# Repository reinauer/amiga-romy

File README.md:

# Amiga Romy

ROMY is a small add-on PCB that enables Amiga 3000 / 4000 computers to use 1MB (or larger) Kickstart chips.

This project aims at iterating and improving the existing Romy designs.

# Software

Look in the [`software`](software/) directory for a bunch of scripts to create a nice 1MB ROM
image for you.

There's also a small program to create parametrized PLCC plug footprints for
KiCAD.

# Logic

The [`logic`](logic/) directory contains the contents for the GAL 22V10. If you want to
build a ROMY yourself, you will need to program this before soldering your GAL
down.

# Hardware

In the [`hardware`](hardware/) directory you will find the kicad schematics and PCB for the
latest versions of ROMY:

## Amiga 4000 Romy

This version was the first one I made. It fits snugly on top of a soldered-down
Fat Gary. The GAL is a PLCC-28 ATF22V10C type. This design is the most similar
to the original Romy.

## Amiga 3000 Romy

This version is a revamp of the A3000 Romy. On the A3000 Fat Gary is socketed
using a through-hole PLCC-84 socket. Previous designs have required to unsolder
the socket, and solder a PCB between a socket and the mainboard, in some
variants adding a capacitor on the bottom of the mainboard.

This new design uses a PLCC-28 ATF22V10C GAL instead of the DIP version on
older Amiga 3000 designs. This is convenient because it lets you exchange GALs
between the A3000 and A4000 version.

To prevent having to solder on the A3000 board, I am using PLCC plugs (such as
the APW9328 from adapt-plus.com).

## Ultimate Romy

Now this gets exciting. PLCC parts are annoying to solder and fairly big. So I
skipped DIP and SOIC and went straight to the TSOP version of the ATF22V10C.
The small footprint of this part allows to create a single board for Amiga 3000
and Amiga 4000 machines.

* If you want to build an A4000 Romy with this design, put a PLCC84 socket on the
back of the PCB, and a capacitor and GAL on the front.
* To build the A3000 version, instead solder a PLCC-84 socket on the front of
the PCB, and solder the cap and GAL on the bottom. Then solder the PLCC plug
over the components.

This design is barely wider than Fat Gary itself and adds the same
functionality as the other ROMYs with minimal impact.

# ROM Extender

The ROM Extender allows the use of 4MB ROM space in an A3000/4000 with the
Ultimate ROMY r6 or newer versions of the A3000 ROMY. You need to connect the
additional address pins between the extender and your ROMY.

When assembling, make sure to optimize for height of the adapter as your
accelerator might have trouble fitting on the A4000.

# Credits

Romy has been developed in the past by speedgeek and Cosmos. Anton Gale kept
the designs alive on OSHPark. Thanks to John Floren for an amazing Amiga 3000,
and to Acill for patiently teaching soldering skills to firmware engineers like
me and for building an awesome community.

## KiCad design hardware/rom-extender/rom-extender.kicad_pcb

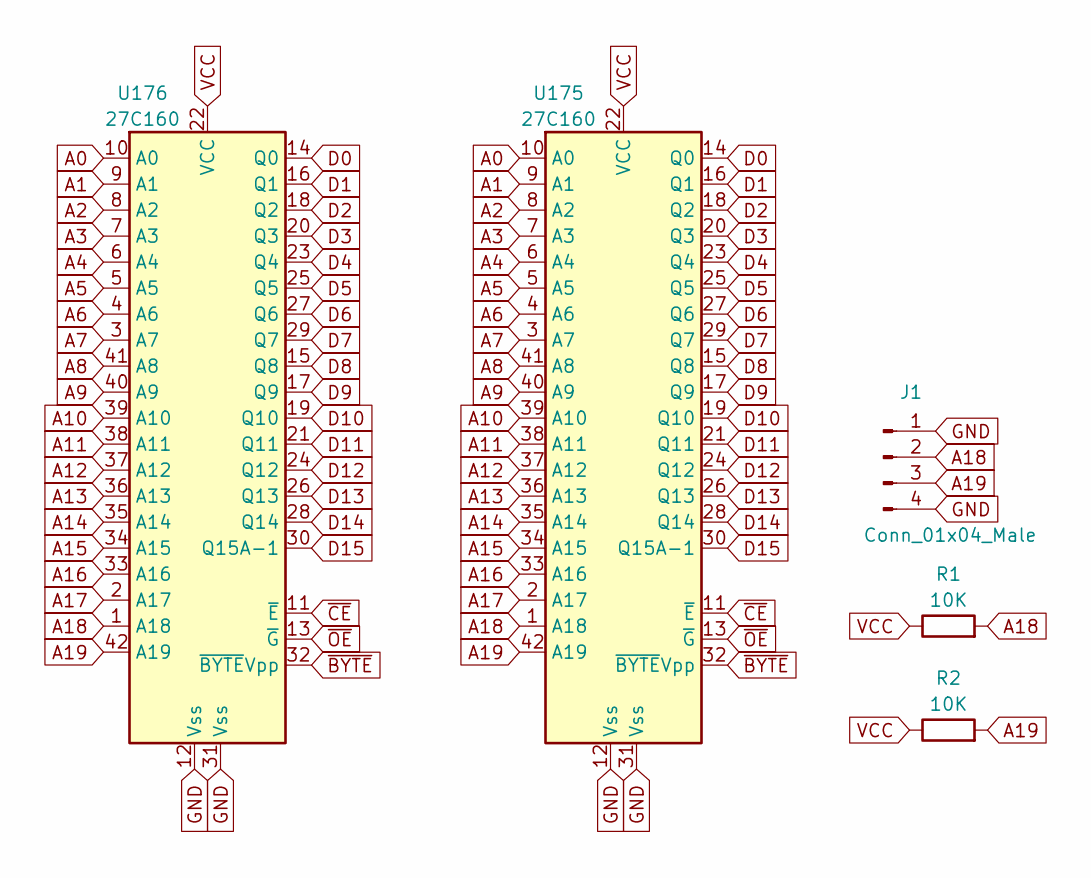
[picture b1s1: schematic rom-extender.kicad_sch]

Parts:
J1: Conn_01x04_Male; PinHeader_1x04_P2.54mm_Vertical
R1, R2: 10K; R_0805_2012Metric_Pad1.20x1.40mm_HandSolder
U175, U176: 27C160; DIP-42_W15.24mm

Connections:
A0: U175.10 (A0), U176.10 (A0)
A1: U175.9 (A1), U176.9 (A1)
A2: U175.8 (A2), U176.8 (A2)
A3: U175.7 (A3), U176.7 (A3)
A4: U175.6 (A4), U176.6 (A4)
A5: U175.5 (A5), U176.5 (A5)
A6: U175.4 (A6), U176.4 (A6)
A7: U175.3 (A7), U176.3 (A7)
A8: U175.41 (A8), U176.41 (A8)
A9: U175.40 (A9), U176.40 (A9)
A10: U175.39 (A10), U176.39 (A10)
A11: U175.38 (A11), U176.38 (A11)
A12: U175.37 (A12), U176.37 (A12)
A13: U175.36 (A13), U176.36 (A13)
A14: U175.35 (A14), U176.35 (A14)
A15: U175.34 (A15), U176.34 (A15)
A16: U175.33 (A16), U176.33 (A16)
A17: U175.2 (A17), U176.2 (A17)
A18: J1.2, R1.2, U175.1 (A18), U176.1 (A18)
A19: J1.3, R2.2, U175.42 (A19), U176.42 (A19)
D0: U175.14 (Q0), U176.14 (Q0)
D1: U175.16 (Q1), U176.16 (Q1)
D2: U175.18 (Q2), U176.18 (Q2)
D3: U175.20 (Q3), U176.20 (Q3)
D4: U175.23 (Q4), U176.23 (Q4)
D5: U175.25 (Q5), U176.25 (Q5)
D6: U175.27 (Q6), U176.27 (Q6)
D7: U175.29 (Q7), U176.29 (Q7)
D8: U175.15 (Q8), U176.15 (Q8)
D9: U175.17 (Q9), U176.17 (Q9)
D10: U175.19 (Q10), U176.19 (Q10)
D11: U175.21 (Q11), U176.21 (Q11)
D12: U175.24 (Q12), U176.24 (Q12)
D13: U175.26 (Q13), U176.26 (Q13)
D14: U175.28 (Q14), U176.28 (Q14)
D15: U175.30 (Q15A-1), U176.30 (Q15A-1)
GND: J1.1, J1.4, U175.12 (Vss), U175.31 (Vss), U176.12 (Vss), U176.31 (Vss)
VCC: R1.1, R2.1, U175.22 (VCC), U176.22 (VCC)
~BYTE: U175.32 (~BYTE~Vpp), U176.32 (~BYTE~Vpp)
~CE: U175.11 (~E), U176.11 (~E)
~OE: U175.13 (~G), U176.13 (~G)

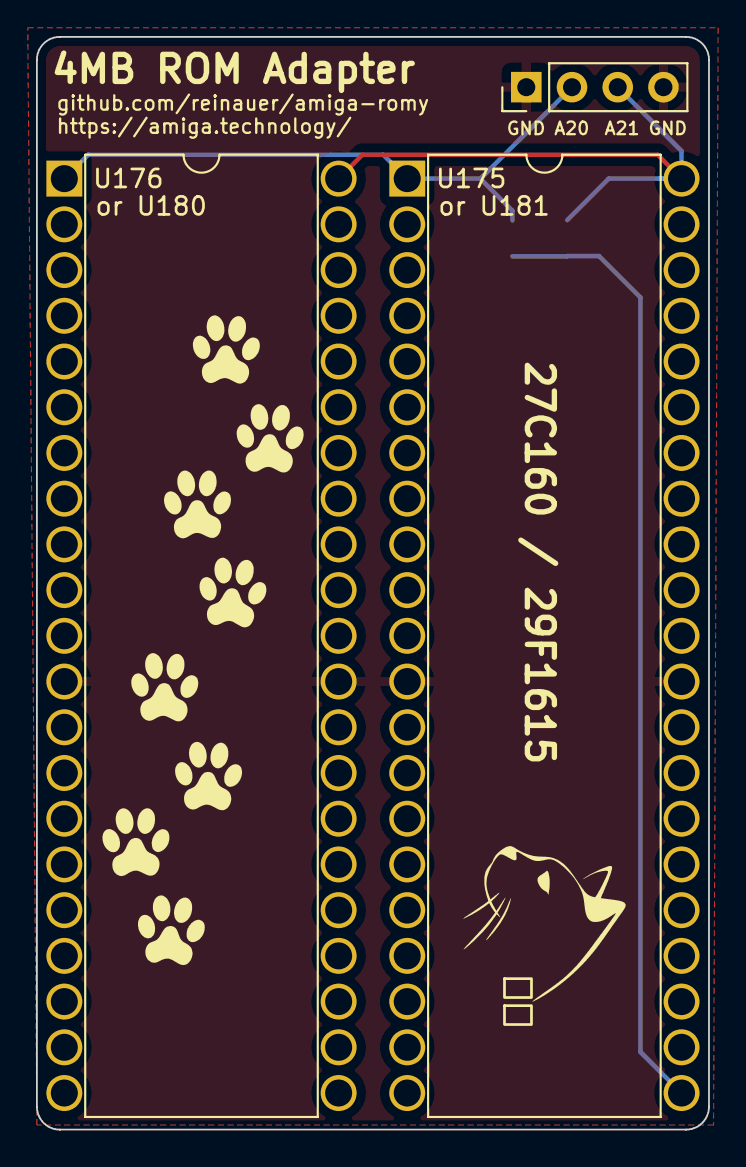
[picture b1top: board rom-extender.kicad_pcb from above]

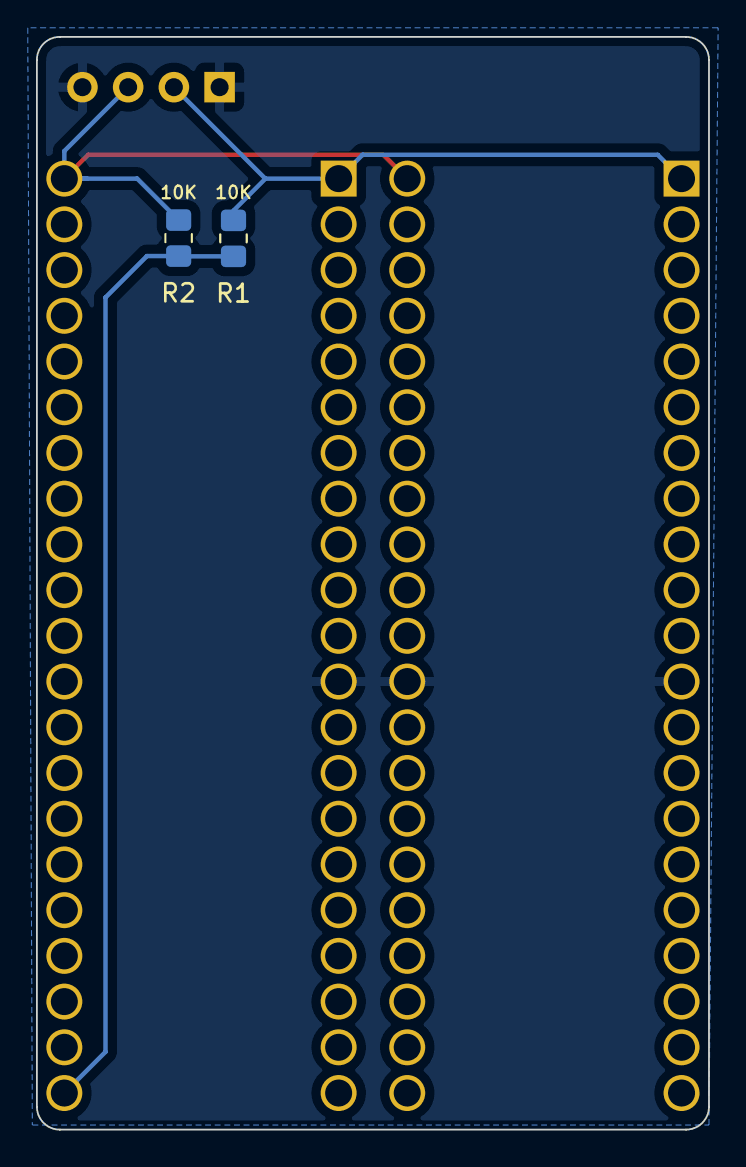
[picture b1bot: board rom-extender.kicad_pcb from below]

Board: 2 copper layers, 37.3 x 60.7 mm, 5 parts (2 on the bottom side), 41 nets.

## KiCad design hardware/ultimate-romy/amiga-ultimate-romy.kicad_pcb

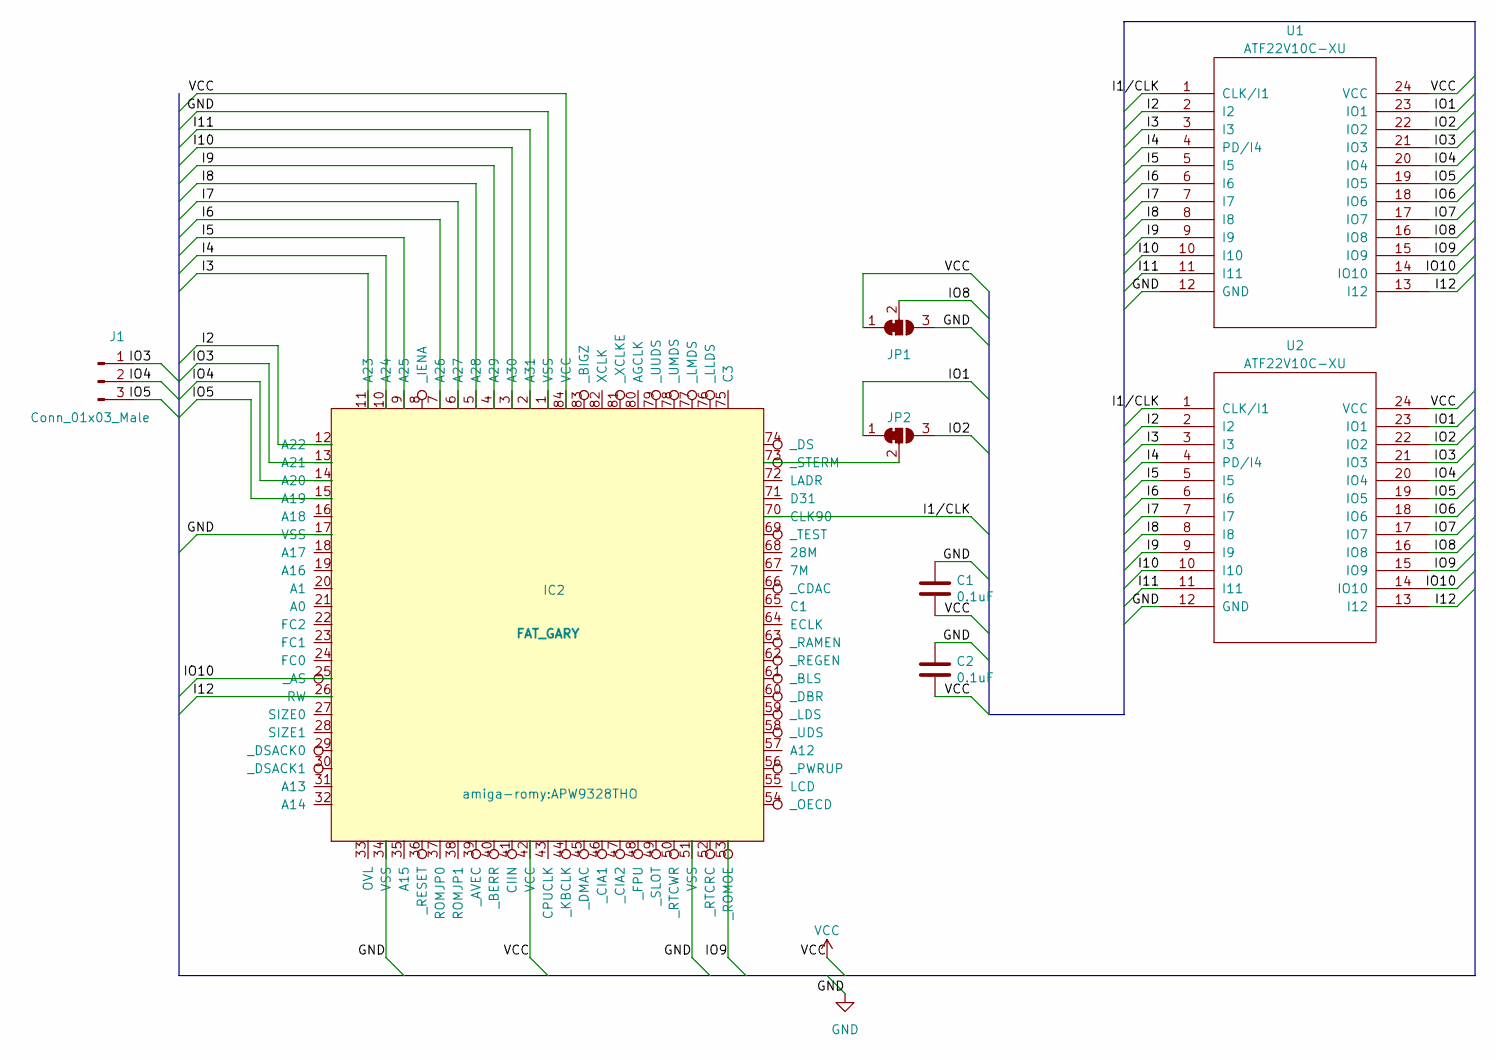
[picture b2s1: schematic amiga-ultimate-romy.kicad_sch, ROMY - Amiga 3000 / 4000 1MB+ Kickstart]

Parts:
C1, C2: 0.1uF; C_0805_2012Metric_Pad1.18x1.45mm_HandSolder
IC2: FAT_GARY; APW9328THO
J1: Conn_01x03_Male; PinHeader_1x03_P2.54mm_Vertical
JP1, JP2: SolderJumper_3_Bridged12; SolderJumper-3_P1.3mm_Bridged12_RoundedPad1.0x1.5mm_NumberL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
U1, U2: ATF22V10C-XU; asym_TSSOP-24_4.4x7.8mm_P0.65mm

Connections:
/I1/CLK: IC2.70 (CLK90), U1.1 (CLK/I1), U2.1 (CLK/I1)
/I2: IC2.12 (A22), U1.2 (I2), U2.2 (I2)
/I3: IC2.11 (A23), U1.3 (I3), U2.3 (I3)
/I4: IC2.10 (A24), U1.4 (PD/I4), U2.4 (PD/I4)
/I5: IC2.9 (A25), U1.5 (I5), U2.5 (I5)
/I6: IC2.7 (A26), U1.6 (I6), U2.6 (I6)
/I7: IC2.6 (A27), U1.7 (I7), U2.7 (I7)
/I8: IC2.5 (A28), U1.8 (I8), U2.8 (I8)
/I9: IC2.4 (A29), U1.9 (I9), U2.9 (I9)
/I10: IC2.3 (A30), U1.10 (I10), U2.10 (I10)
/I11: IC2.2 (A31), U1.11 (I11), U2.11 (I11)
/I12: IC2.26 (RW), U1.13 (I12), U2.13 (I12)
/IO1: JP2.1 (A), U1.23 (IO1), U2.23 (IO1)
/IO2: JP2.3 (B), U1.22 (IO2), U2.22 (IO2)
/IO3: IC2.13 (A21), J1.1, U1.21 (IO3), U2.21 (IO3)
/IO4: IC2.14 (A20), J1.2, U1.20 (IO4), U2.20 (IO4)
/IO5: IC2.15 (A19), J1.3, U1.19 (IO5), U2.19 (IO5)
/IO6: U1.18 (IO6), U2.18 (IO6)
/IO7: U1.17 (IO7), U2.17 (IO7)
/IO8: JP1.2 (C), U1.16 (IO8), U2.16 (IO8)
/IO9: IC2.53 (_ROMOE), U1.15 (IO9), U2.15 (IO9)
/IO10: IC2.25 (_AS), U1.14 (IO10), U2.14 (IO10)
GND: C1.1, C2.1, IC2.1 (VSS), IC2.17 (VSS), IC2.34 (VSS), IC2.51 (VSS), JP1.3 (B), U1.12 (GND), U2.12 (GND)
unnamed: IC2.73 (_STERM), JP2.2 (C)
VCC: C1.2, C2.2, IC2.42 (VCC), IC2.84 (VCC), JP1.1 (A), U1.24 (VCC), U2.24 (VCC)

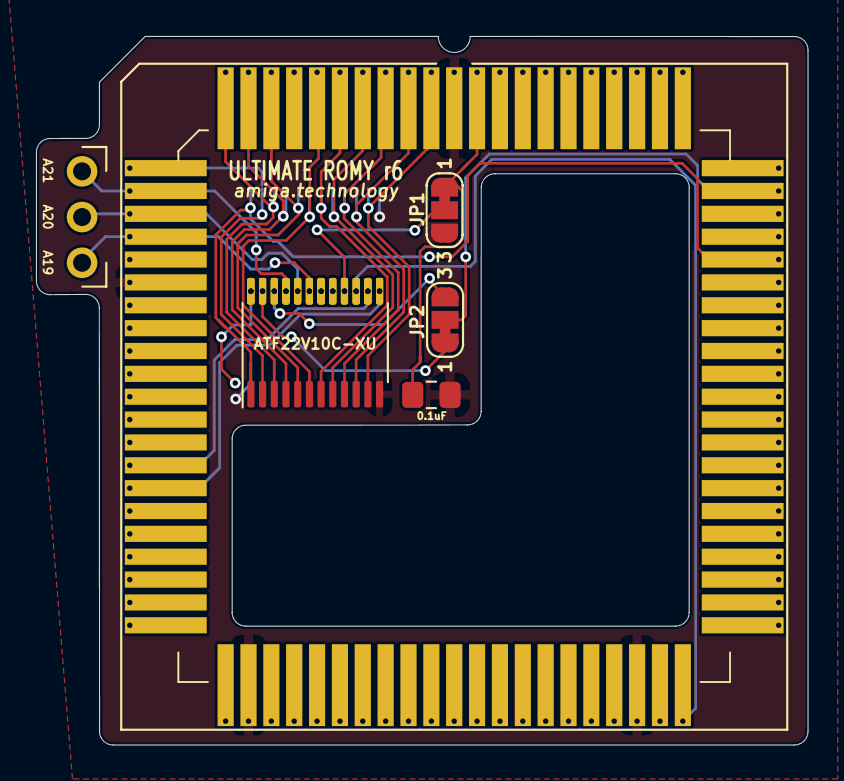
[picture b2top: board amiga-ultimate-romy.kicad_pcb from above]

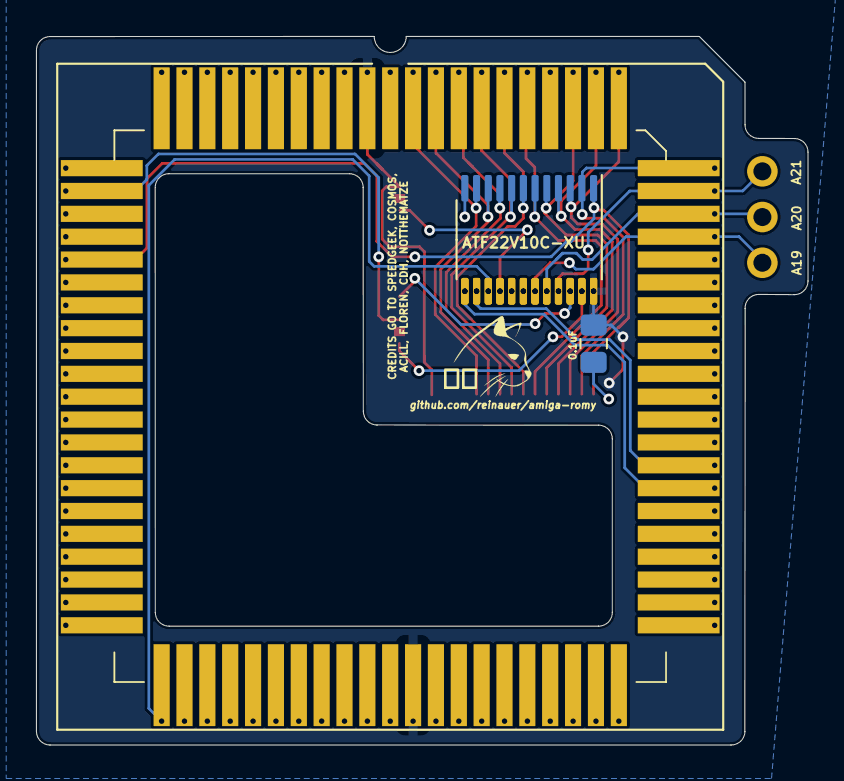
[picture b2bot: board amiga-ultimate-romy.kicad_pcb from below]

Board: 2 copper layers, 42.9 x 39.4 mm, 9 parts (3 on the bottom side), 25 nets.

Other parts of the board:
カツ: Katsu

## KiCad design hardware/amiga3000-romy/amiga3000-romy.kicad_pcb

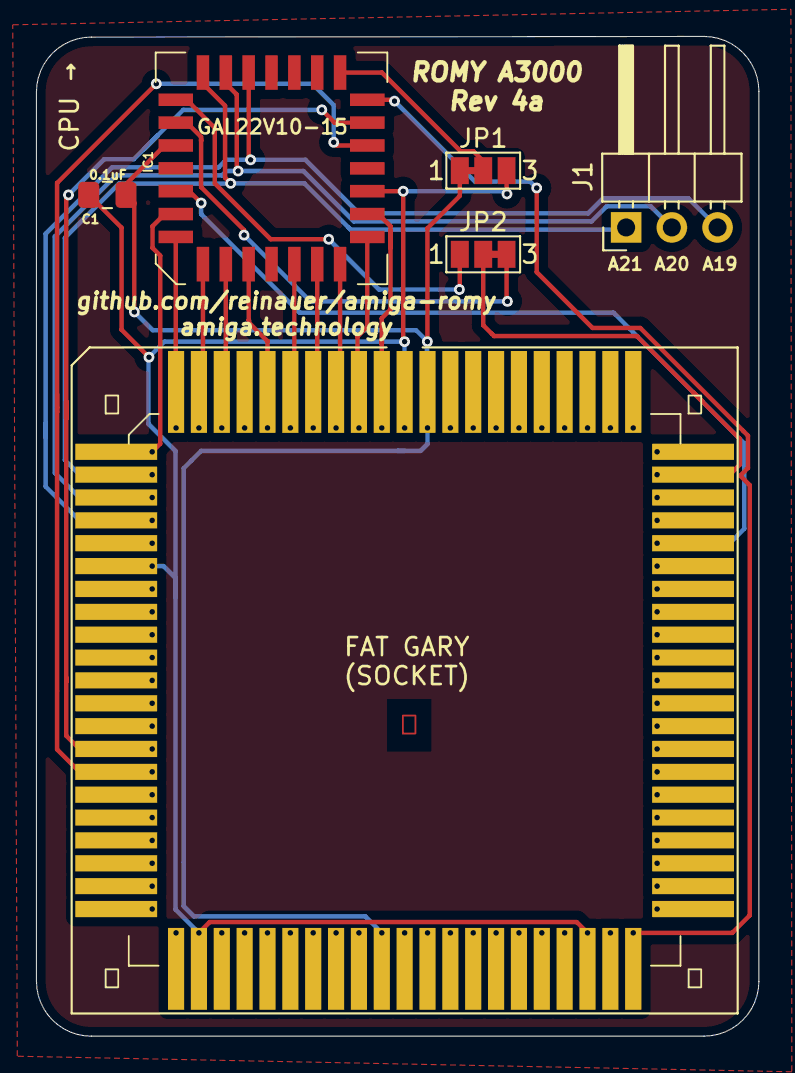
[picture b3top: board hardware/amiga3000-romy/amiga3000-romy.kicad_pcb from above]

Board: 2 copper layers, 40.1 x 55.5 mm, 6 parts (1 on the bottom side), 23 nets.

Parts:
C1: 0.1uF; C_0805_2012Metric_Pad1.18x1.45mm_HandSolder
IC1: GAL22V10; PLCC-28
IC2: FAT_GARY; APW9328TH
J1: Conn_01x03_Male; PinHeader_1x03_P2.54mm_Horizontal
JP1: SolderJumper_3_Open; SolderJumper-3_P1.3mm_Closed_12_Pad1.0x1.5mm_NumberLabels
JP2: SolderJumper_3_Open; SolderJumper-3_P1.3mm_Closed_23_Pad1.0x1.5mm_NumberLabels

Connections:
unnamed: C1.1, IC1.14 (GND), IC2.1 (VSS), IC2.17 (VSS), IC2.34 (VSS), IC2.51 (VSS), JP1.3 (B)
unnamed: C1.2, IC1.28 (VCC), IC2.42 (VCC), IC2.84 (VCC), JP1.1 (A)
unnamed: IC1.2 (I1/CLK), IC2.70 (CLK90)
unnamed: IC1.3 (I2), IC2.12 (A22)
unnamed: IC1.4 (I3), IC2.11 (A23)
unnamed: IC1.5 (I4), IC2.10 (A24)
unnamed: IC1.6 (I5), IC2.9 (A25)
unnamed: IC1.7 (I6), IC2.7 (A26)
unnamed: IC1.9 (I7), IC2.6 (A27)
unnamed: IC1.10 (I8), IC2.5 (A28)
unnamed: IC1.11 (I9), IC2.4 (A29)
unnamed: IC1.12 (I10), IC2.3 (A30)
unnamed: IC1.13 (I11), IC2.2 (A31)
unnamed: IC1.16 (I12), IC2.26 (RW)
unnamed: IC1.17 (IO10), IC2.25 (_AS)
unnamed: IC1.18 (IO9), IC2.53 (_ROMOE)
unnamed: IC1.19 (IO8), JP1.2 (C)
unnamed: IC1.23 (IO5), IC2.15 (A19), J1.3
unnamed: IC1.24 (IO4), IC2.14 (A20), J1.2
unnamed: IC1.25 (IO3), IC2.13 (A21), J1.1
unnamed: IC1.26 (IO2), JP2.1 (A)
unnamed: IC1.27 (IO1), JP2.3 (B)
unnamed: IC2.73 (_STERM), JP2.2 (C)

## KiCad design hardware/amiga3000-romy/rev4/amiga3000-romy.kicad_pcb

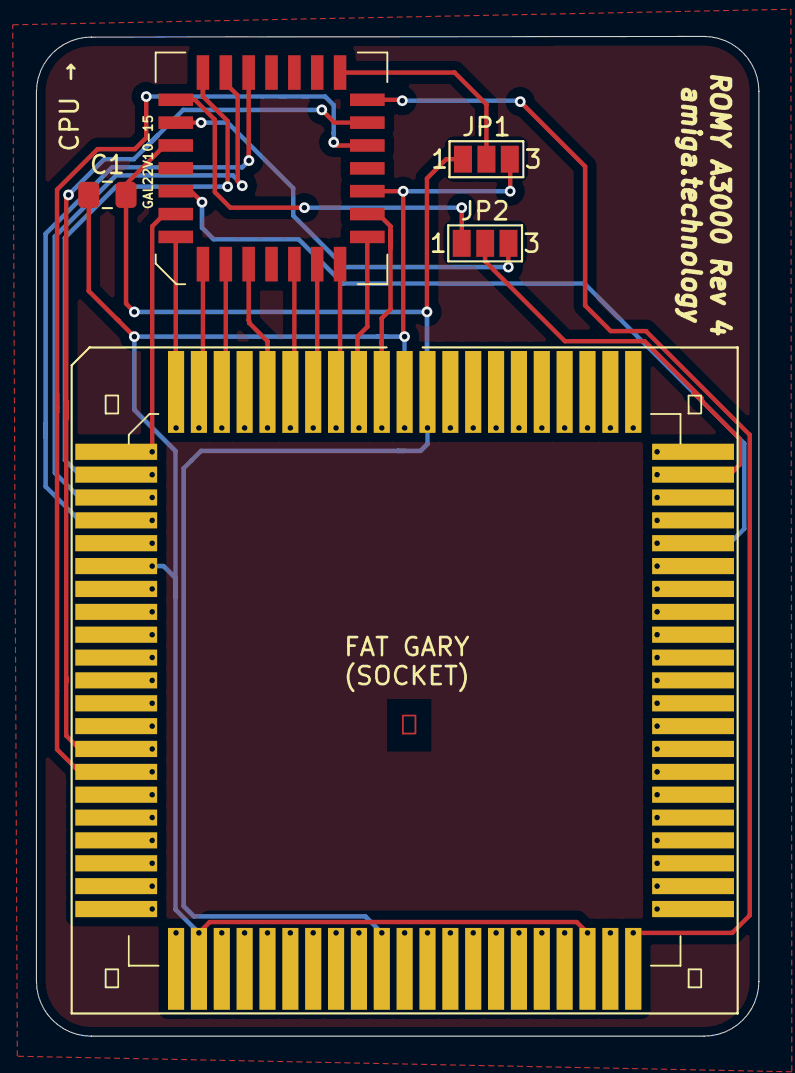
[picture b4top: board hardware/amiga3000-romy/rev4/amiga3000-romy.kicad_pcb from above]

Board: 2 copper layers, 40.1 x 55.5 mm, 5 parts (1 on the bottom side), 23 nets.

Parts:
 : FAT_GARY; APW9328TH
C1: 0.1uF; C_0805_2012Metric_Pad1.18x1.45mm_HandSolder
GAL22V10-15: GAL22V10; PLCC-28
JP1, JP2: SolderJumper_3_Open; SolderJumper-3_P1.3mm_Open_Pad1.0x1.5mm_NumberLabels

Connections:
unnamed: .1 (VSS), .17 (VSS), .34 (VSS), .51 (VSS), C1.1, GAL22V10-15.14 (GND), JP1.3 (B)
unnamed: .42 (VCC), .84 (VCC), C1.2, GAL22V10-15.28 (VCC), JP1.1 (A)
unnamed: .70 (CLK90), GAL22V10-15.2 (I1/CLK)
unnamed: .12 (A22), GAL22V10-15.3 (I2)
unnamed: .11 (A23), GAL22V10-15.4 (I3)
unnamed: .10 (A24), GAL22V10-15.5 (I4)
unnamed: .9 (A25), GAL22V10-15.6 (I5)
unnamed: .7 (A26), GAL22V10-15.7 (I6)
unnamed: .6 (A27), GAL22V10-15.9 (I7)
unnamed: .5 (A28), GAL22V10-15.10 (I8)
unnamed: .4 (A29), GAL22V10-15.11 (I9)
unnamed: .3 (A30), GAL22V10-15.12 (I10)
unnamed: .2 (A31), GAL22V10-15.13 (I11)
unnamed: .26 (RW), GAL22V10-15.16 (I12)
unnamed: .25 (_AS), GAL22V10-15.17 (IO10)
unnamed: .53 (_ROMOE), GAL22V10-15.18 (IO9)
unnamed: GAL22V10-15.19 (IO8), JP1.2 (C)
unnamed: .15 (A19), GAL22V10-15.23 (IO5)
unnamed: .14 (A20), GAL22V10-15.24 (IO4)
unnamed: .13 (A21), GAL22V10-15.25 (IO3)
unnamed: GAL22V10-15.26 (IO2), JP2.1 (A)
unnamed: GAL22V10-15.27 (IO1), JP2.3 (B)
unnamed: .73 (_STERM), JP2.2 (C)

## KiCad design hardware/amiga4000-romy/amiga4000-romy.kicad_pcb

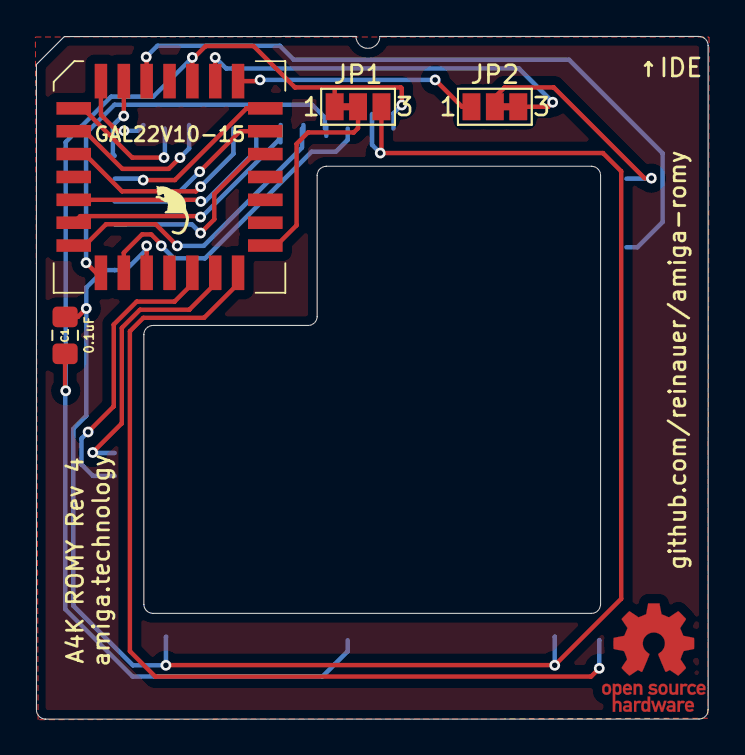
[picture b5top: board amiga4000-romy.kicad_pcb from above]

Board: 2 copper layers, 37.3 x 37.9 mm, 5 parts (1 on the bottom side), 23 nets.

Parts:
C1: 0.1uF; C_0805_2012Metric_Pad1.15x1.40mm_HandSolder
FAT GARY: FAT_GARY; PLCC-84_SMD-Socket_mirrored
GAL22V10-15: GAL22V10; PLCC-28
JP1: SolderJumper_3_Open; SolderJumper-3_P1.3mm_Closed_12_Pad1.0x1.5mm_NumberLabels
JP2: SolderJumper_3_Open; SolderJumper-3_P1.3mm_Closed_23_Pad1.0x1.5mm_NumberLabels

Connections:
unnamed: C1.1, FAT GARY.1, FAT GARY.17, FAT GARY.34, FAT GARY.51, GAL22V10-15.14, JP1.3
unnamed: C1.2, FAT GARY.42, FAT GARY.84, GAL22V10-15.28, JP1.1
unnamed: FAT GARY.70, GAL22V10-15.2
unnamed: FAT GARY.12, GAL22V10-15.3
unnamed: FAT GARY.11, GAL22V10-15.4
unnamed: FAT GARY.10, GAL22V10-15.5
unnamed: FAT GARY.9, GAL22V10-15.6
unnamed: FAT GARY.7, GAL22V10-15.7
unnamed: FAT GARY.6, GAL22V10-15.9
unnamed: FAT GARY.5, GAL22V10-15.10
unnamed: FAT GARY.4, GAL22V10-15.11
unnamed: FAT GARY.3, GAL22V10-15.12
unnamed: FAT GARY.2, GAL22V10-15.13
unnamed: FAT GARY.26, GAL22V10-15.16
unnamed: FAT GARY.25, GAL22V10-15.17
unnamed: FAT GARY.53, GAL22V10-15.18
unnamed: GAL22V10-15.19, JP1.2
unnamed: FAT GARY.15, GAL22V10-15.23
unnamed: FAT GARY.14, GAL22V10-15.24
unnamed: FAT GARY.13, GAL22V10-15.25
unnamed: GAL22V10-15.26, JP2.1
unnamed: GAL22V10-15.27, JP2.3
unnamed: FAT GARY.73, JP2.2

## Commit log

2021-03-28 Initial release
2021-03-28 Add rendered image
2021-03-28 Add photo of installed ROMY
2021-04-01 Add scripts to create 1MB ROM image for A4000D
2021-04-01 Use IMG tag for pictures
2021-04-01 Improve documentation
2021-04-18 Move current version to amiga4000-romy subdirectory
2021-04-18 Add footprint generator for PLCC plugs
    I've been using adapt-plus.com's APW9328 PLCC plugs
    for ROMY designs for the machines that have socketed
    PLCC84 chips. Because I suck at Deluxe Paint and other
    graphics tools, I wrote a little program that lets me
    parametrize these PLCC plugs the way I need them.
2021-04-18 Add Amiga 3000 version of the "new" ROMY
2021-04-18 Ultimate ROMY initial version
2021-04-18 Update README.md to reflect other variants
2021-04-18 Mention PLCC plug footprint generator in documentation
2021-04-25 Minor update to A4000 ROMY
    - rounder edges
    - slightly better routing
    - preset jumpers for two less solder joints
    - move to KiCAD 6.0rc
2021-04-26 Add .gitignore
2021-05-13 Allow creating non-A4000 images
    - Update build.sh to work with all 3.1.4 images (most likely)
    - integrate srec_cat calls directly as they're used differently
    than arom2bin (and hence remove arom2bin and arom2bin_slim)
    Thank you to faxm0dem (Fabien Wernli) for this super useful tool.
    - Add build target to test production of 1MB ROMs for all Amigas
    (Sorry, only build.sh is adjusted at this point, you will have
2021-05-13 software: allow other OS versions
    - allow the use of versions other than 46.143
    - factor out additional module selection so we can
    add additional modules more easily (e.g. IDE for TF1260)
2021-05-13 software: make build script more resilient
    3.1.4 ROMs exist in a (A4000) and (A4000_R2) version.
    Make this script more resilient so we don't have to bother
2021-05-13 software: README.md should be markdown syntax
    All these years with mediawiki left their mark on my brain.
2021-05-17 Support for Amiga OS 3.2
2021-05-17 clean up hrtmon compilation
2021-05-25 Support for building 2MB/4MB images
    This will need a newer amitools/romtool version with the 4mb_rom
    support merged.
2021-06-02 Copy Amiga 3000 files to rev4 directory
2021-06-02 Update Amiga3000 ROMY to Rev4a
    major difference is the address header to support 4MB ROMs
2021-06-02 Create copy of Ultimate ROMY rev5
2021-06-02 Update Ultimate ROMY to Rev6
    - Reroute the board to use 6mil instead of 5mil traces.
    This will make the boards significantly cheaper with some fab houses
    - Add address pins for 4MB support
    - Move vias in PLCC footprint to the outside to prevent solder paste
    from leaking to the other side when using hot air to assemble socket
    on A4000 version
2021-06-02 Remove experimental note
2021-06-02 Add 4MB capable ROM extender board
    This board lets you connect two additional pins to newer ROMY revisions
    for 2MB and 4MB ROMs. It can also serve as a simple kickstart switcher
    by itself.
    For Amiga 3000 I recommed http://eebugs.com/amiga/rombankswitcher3000rt/
    Or http://eebugs.com/amiga/rombankswitcher3000/ (version with / without ROM
    tower) made by Chris Hooper.
2021-06-03 Update footprint generator
    - put silkscreen on both sides
    - allow via placement
2021-06-03 Fix ehide.device inclusion
    This will add a warning guru and a long delay to your boot time.
2021-06-26 Some intermediate files for analysing ROMY .jed
2021-06-26 Make Makefile more useful
    - per default it will print help now
    - allow to specify targets, sizes, and version when calling the
    Makefile
2021-06-26 Hook up romdisk
    This will more or less require a large ROM (2/4MB) or a very
    small romdisk :)
2021-06-27 Makefile: Make output more useful
2021-06-27 Add modules support to build system
    This makes the build system a lot more flexible and clean.
    As an example I added arp.library and explode.library modules.
2021-06-27 Update README.md to reflect current software
2021-06-27 Fix module path
2021-06-28 Add simple configuration system
    With more modules being available, it would be nice to turn them on
    individually. Particularly on 1MB ROMYs you can't fit all modules into
    the ROM anymore. See amiga-romy.conf for available options.
    Also add a bunch of libraries and filesystems as plugin modules.
    Contributions welcome!
2021-06-28 Fix ehide.device
2021-06-28 make config file executable
2021-06-28 Add script to create CD32 ROMs
2021-06-29 Print the correct(?) chip
    Try to suggest the right chips for programming
2021-06-29 make test targets more robust
2021-07-08 Add simple debugging mechanism
2021-07-08 Add compile hook to modules
2021-07-08 Factor hrtmon, romdisk and ehide.device into modules
2021-07-08 Don't download ehide.device twice
2021-07-08 Add EQN files with renamed pins
2021-07-18 Update software README
2021-07-28 Whoops.
2021-08-13 added check for required programs
2021-08-13 readme
2021-12-31 Add support for AmigaOS 3.2.1 (47.102)
2022-09-08 Make kickstart rom builder work on MacOSX
    This is a pretty big overhaul of the script, that should also benefit
    Linux users:
    - Drop the use of unadf in favor of xdftool which is already installed
    though amitools as we are also using romtool.
    - Don't loopback mount the ISO images but use 7z to extract files. This
    works on non-Linux platforms.
2022-09-08 Mention ROM extender on main page
2022-12-26 Clean up help output
2022-12-26 Fix ext2 plugin
2022-12-26 Disable CDFileSystem for now, it is not ROMable
2022-12-29 Add source file to compile logic from scratch
2022-12-29 Add some more modules
